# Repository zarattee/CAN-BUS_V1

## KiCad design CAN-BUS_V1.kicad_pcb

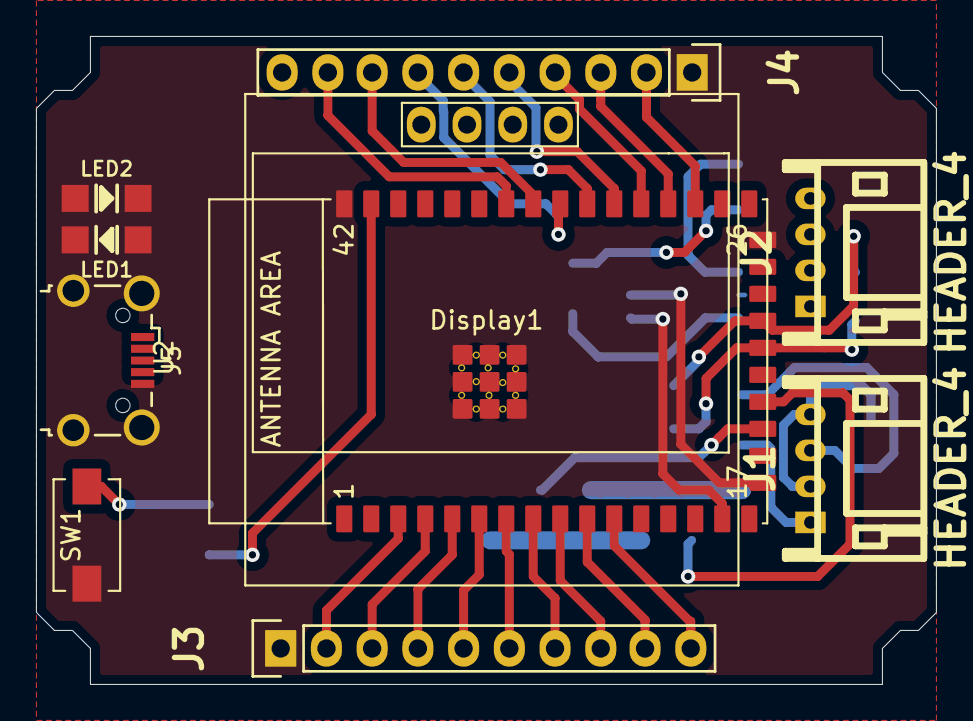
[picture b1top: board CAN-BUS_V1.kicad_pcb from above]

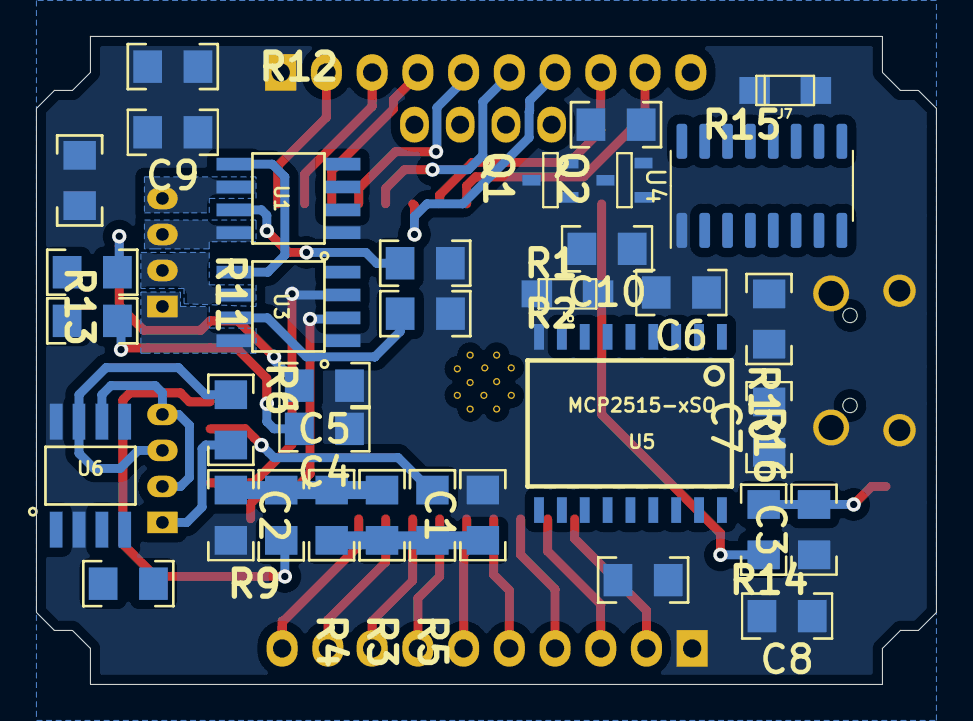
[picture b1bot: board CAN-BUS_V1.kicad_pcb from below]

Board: 2 copper layers, 50.0 x 36.0 mm, 45 parts (35 on the bottom side), 56 nets.

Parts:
C1, C2, C3, C4, C5, C6, C7, C8, C9, C10: C; C_1206
Display1: SSD1306-SSD1306-128x64_OLED; 128x64OLED
J1, J2: HEADER_4; JST-4H
J3, J4: HEADER_10; Pin_Header_Straight_1x10
J5: USB_B_Micro; USB_Micro-B_Wuerth_629105150521_CircularHoles
J6, J7: HEADER_2; CAP_TAN_A
LED1, LED2: LED; LED_1206
Q1, Q2: BC847; SOT23
R1, R2, R3, R4, R5, R6, R7, R8, R9, R10, R11, R12, R13, R14, R15, R16: R; R_1206
SW1: SW_Push; SW_SPST_EVQPE1
U1, U3: DRV8872; SSOP-8
U2: esp32-s2-wroom; esp32-s2-wrooom
U4: CH340G; SOIC-16_3.9x9.9mm_P1.27mm
U5: MCP2515-xSO; SOIC-18
U6: TJA1050; SOIC-8_Hand_Soldering

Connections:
/A_OUT1: J2.4, U1.6
/A_OUT2: J2.3, U1.8
/B_OUT1: J2.2, U3.6
/B_OUT2: J2.1, U3.8
/EN: Q1.2, R10.1, U2.41
/IO0: J3.2, Q2.3
/IO2: J3.4, U2.5
/IO3: J3.5, U2.6
/IO4: J3.6, U2.7
/IO5: J3.7, U2.8
/IO6: J3.8, U2.9
/IO7: J3.9, U2.10
/IO8: J3.10, U2.11
/IO35: J4.2, U2.29
/IO36: J4.3, U2.30
/IO37: J4.4, U2.31
/IO38: J4.5, U2.32
/IO39: J4.6, U2.33
/IO40: J4.7, U2.34
/IO41: J4.8, U2.35
/IO42: J4.9, U2.36
/M1A: U1.3, U2.4
/M1B: U1.2, U2.3
/M2A: U2.17, U3.3
/M2B: U2.15, U3.2
/VIN: U1.5, U3.5
/dtr: Q2.2, R15.1, U4.13
/rts: Q1.3, R16.1, U4.14
/rx: LED1.2, U4.3
/tx: LED2.2, U4.2
/x0: C6.2, C7.2, J6.1, J6.2, U4.8
GND: C1.1, C2.1, C3.2, C4.2, C5.2, C6.1, C7.1, C8.1, C9.1, C10.1, J3.1, J4.1, J5.5, J5.6, R1.2, R2.2, SW1.1, U1.1, U2.26, U2.42, U2.43, U3.1, U4.1, U5.9, U6.2, U6.8
unnamed: C1.2, R3.2, R4.2, R5.2
unnamed: C2.2, R3.1, R4.1, R6.2
unnamed: C3.1, R10.2, SW1.2
unnamed: C4.1, R7.1, U2.22
unnamed: C5.1, R8.1, U2.23
unnamed: C8.2, J7.2, U5.7
unnamed: C9.2, J7.1, U5.8
unnamed: J1.1, R11.1
unnamed: J1.2, J1.4, U6.6
unnamed: J1.3, R11.2, U6.7
unnamed: J5.2, U4.6
unnamed: J5.3, U4.5
unnamed: LED1.1, R13.1
unnamed: LED2.1, R14.1
unnamed: Q1.1, R15.2
unnamed: Q2.1, R16.2
unnamed: R1.1, U1.7
unnamed: R2.1, U3.7
unnamed: R5.1, U2.19
unnamed: R6.1, U2.20
unnamed: R9.2, U2.21
unnamed: U5.1, U6.1
unnamed: U5.2, U6.4
VDD: C10.2, J4.10, R9.1, R12.2, R13.2, R14.2, U4.4, U4.16, U6.3

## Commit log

2020-12-27 modificacione
    se agregaron nueva conexiones y carpetas con imagenes de referencia
2021-07-07 MODIFICACIONES
    se modifico sch,pcb y se elimino un archivo jpg
